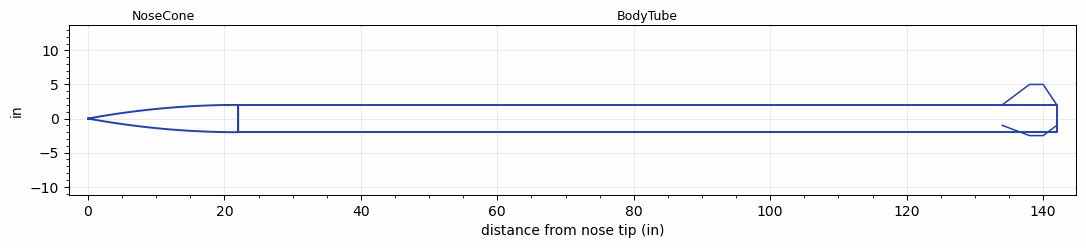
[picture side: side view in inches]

<RASAeroDocument>
 <FileVersion>2</FileVersion>
 <RocketDesign>
  <NoseCone>
   <Length>22</Length>
   <Diameter>4</Diameter>
   <Shape>Tangent Ogive</Shape>
   <Location>0</Location>
  </NoseCone>
  <BodyTube>
   <Length>120</Length>
   <Diameter>4</Diameter>
   <Location>22</Location>
   <Fin>
    <Count>3</Count>
    <Chord>8</Chord>
    <Span>3</Span>
    <SweepDistance>4</SweepDistance>
    <TipChord>2</TipChord>
    <Thickness>0.25</Thickness>
    <LERadius>0.125</LERadius>
    <Location>8</Location>
    <AirfoilSection>Double Wedge</AirfoilSection>
    <FX1>1</FX1>
    <FX3>1</FX3>
   </Fin>
  </BodyTube>
  <Surface>Smooth Paint</Surface>
  <ModifiedBarrowman>False</ModifiedBarrowman>
  <Turbulence>False</Turbulence>
  <UseBooster1>False</UseBooster1>
  <UseBooster2>False</UseBooster2>
 </RocketDesign>
 <LaunchSite>
  <Altitude>5000</Altitude>
  <Pressure>0</Pressure>
  <RodAngle>3</RodAngle>
  <RodLength>10</RodLength>
  <Temperature>95</Temperature>
  <WindSpeed>20</WindSpeed>
 </LaunchSite>
 <Recovery>
  <Altitude1>1000</Altitude1>
  <Altitude2>1000</Altitude2>
  <DeviceType1>None</DeviceType1>
  <DeviceType2>None</DeviceType2>
  <Event1>False</Event1>
  <Event2>False</Event2>
  <Size1>1</Size1>
  <Size2>1</Size2>
  <EventType1>None</EventType1>
  <EventType2>None</EventType2>
  <CD1>1.33</CD1>
  <CD2>1.33</CD2>
 </Recovery>
 <SimulationList>
  <Simulation>
   <SustainerEngine>N2900-CL  (CTI)</SustainerEngine>
   <SustainerLaunchWt>61</SustainerLaunchWt>
   <SustainerNozzleDiameter>1.5</SustainerNozzleDiameter>
   <SustainerCG>80</SustainerCG>
   <SustainerIgnitionDelay>0</SustainerIgnitionDelay>
   <Booster1SeparationDelay>0</Booster1SeparationDelay>
   <Booster1IgnitionDelay>0</Booster1IgnitionDelay>
   <IncludeBooster1>False</IncludeBooster1>
   <Booster2Delay>0</Booster2Delay>
   <IncludeBooster2>False</IncludeBooster2>
   <TimetoApogee>42.04895</TimetoApogee>
   <MaxAltitude>31988.9</MaxAltitude>
   <MaxVelocity>1999.129</MaxVelocity>
   <OptimumWt>34.3373</OptimumWt>
   <OptimumMaxAlt>34.3373</OptimumMaxAlt>
  </Simulation>
  <Simulation>
   <SustainerEngine>N2900-CL  (CTI)</SustainerEngine>
   <SustainerLaunchWt>61</SustainerLaunchWt>
   <SustainerNozzleDiameter>1.5</SustainerNozzleDiameter>
   <SustainerCG>81</SustainerCG>
   <SustainerIgnitionDelay>0</SustainerIgnitionDelay>
   <Booster1SeparationDelay>0</Booster1SeparationDelay>
   <Booster1IgnitionDelay>0</Booster1IgnitionDelay>
   <IncludeBooster1>False</IncludeBooster1>
   <Booster2Delay>0</Booster2Delay>
   <IncludeBooster2>False</IncludeBooster2>
   <TimetoApogee>48.14793</TimetoApogee>
   <MaxAltitude>40288.09</MaxAltitude>
   <MaxVelocity>2057.845</MaxVelocity>
   <OptimumWt>34.3373</OptimumWt>
   <OptimumMaxAlt>34.3373</OptimumMaxAlt>
  </Simulation>
 </SimulationList>
</RASAeroDocument>
